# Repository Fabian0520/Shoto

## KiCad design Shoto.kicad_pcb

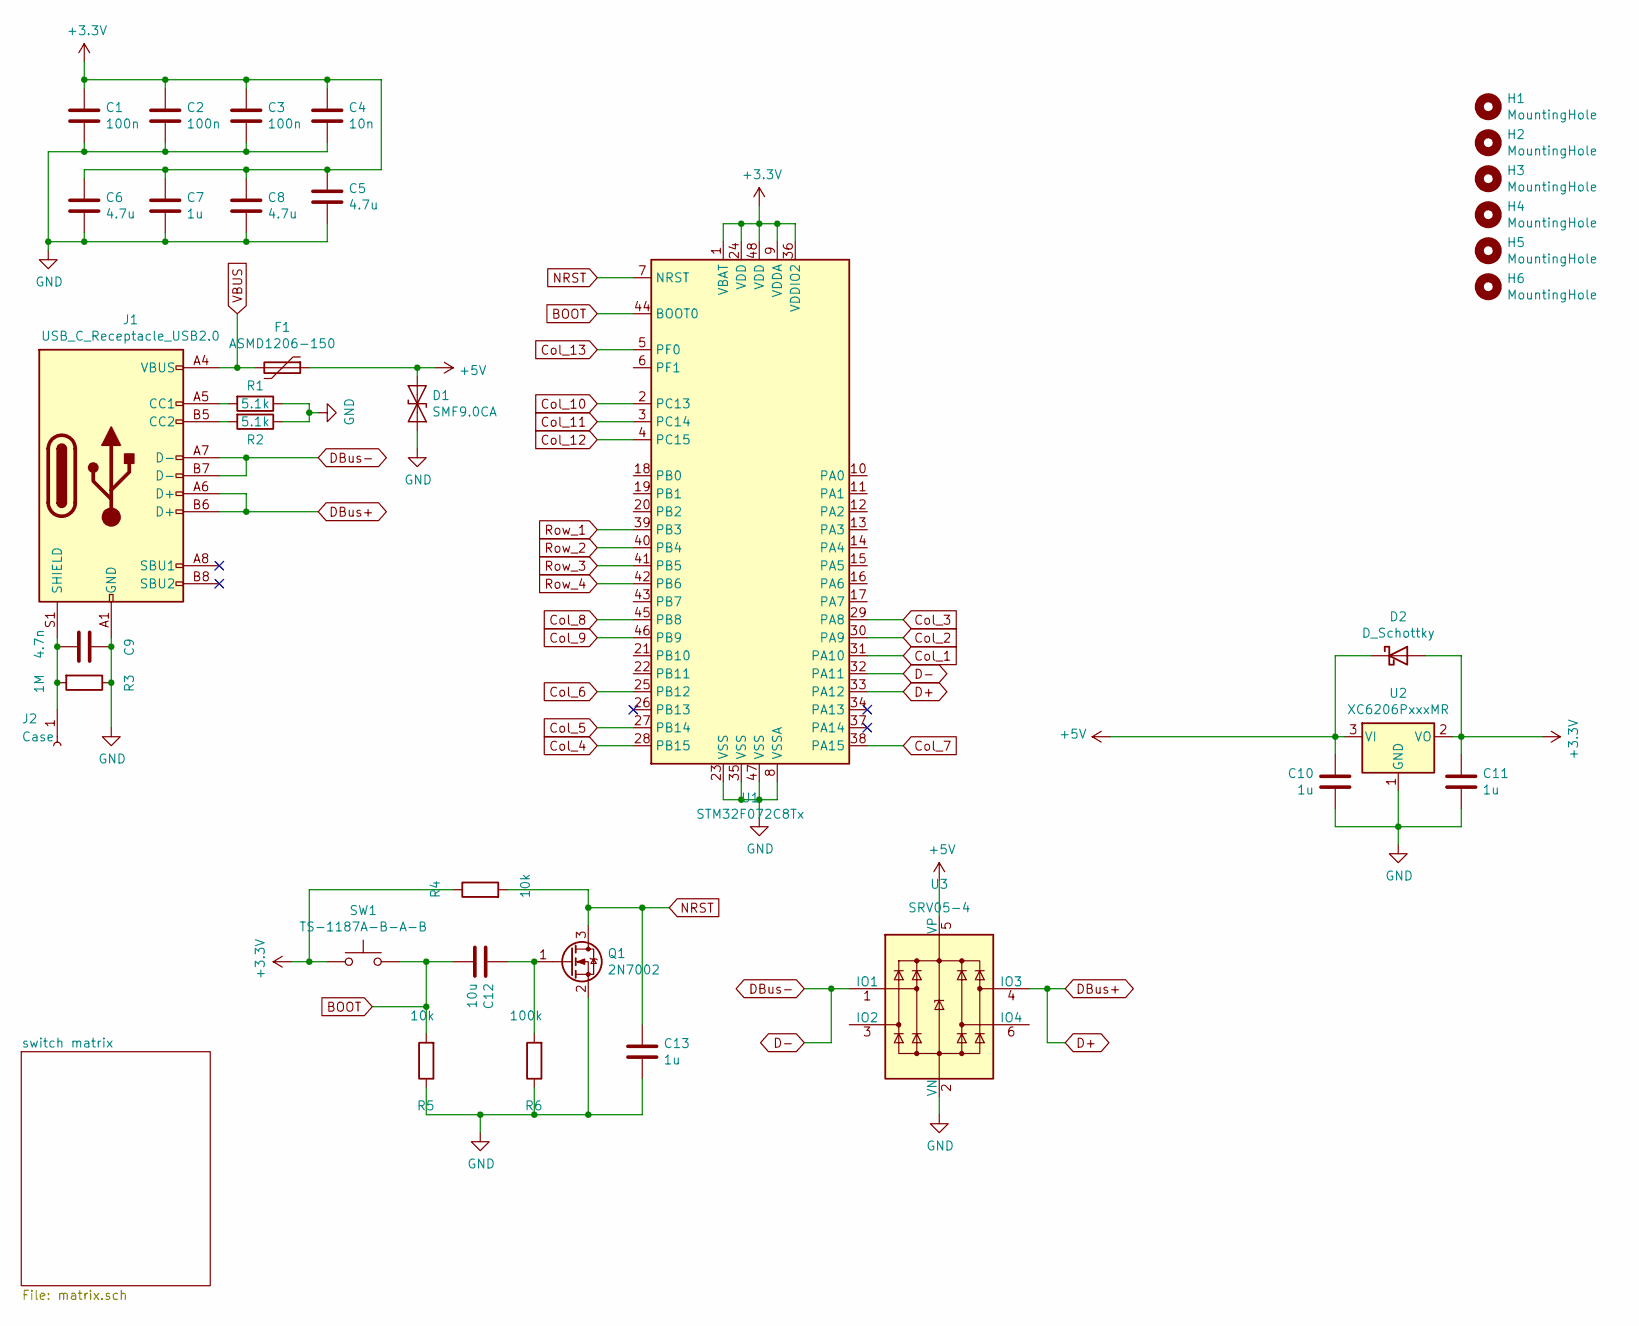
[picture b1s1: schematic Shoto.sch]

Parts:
C1, C2, C3: 100n; C_0603_1608Metric; JLCPCB C14663
C4: 10n; C_0603_1608Metric; JLCPCB C57112
C5, C6, C8: 4.7u; C_0603_1608Metric; JLCPCB C19666
C7, C10, C11, C13: 1u; C_0603_1608Metric; JLCPCB C15849
C9: 4.7n; C_0603_1608Metric; JLCPCB C53987
C12: 10u; C_0603_1608Metric; JLCPCB C19702
D1: SMF9.0CA; D_SOD-123; JLCPCB C123799
D2: D_Schottky; D_SOD-123; JLCPCB C8598
F1: ASMD1206-150; Fuse_1206_3216Metric; JLCPCB C135341
H1, H2, H3, H4, H5, H6: MountingHole; MountingHole_2.2mm_M2
J1: USB_C_Receptacle_USB2.0; USB_C_Receptacle_HRO_TYPE-C-31-M-12
J2: Case; MountingHole_2.2mm_M2_Pad
Q1: 2N7002; SOT-23; JLCPCB C8545
R1, R2: 5.1k; R_0603_1608Metric; JLCPCB C23186
R3: 1M; R_1206_3216Metric; JLCPCB C17927
R4, R5: 10k; R_0603_1608Metric; JLCPCB C25804
R6: 100k; R_0603_1608Metric; JLCPCB C25803
SW1: TS-1187A-B-A-B; SW_SPST_TL3342; JLCPCB C318884
U1: STM32F072C8Tx; LQFP-48_7x7mm_P0.5mm; JLCPCB C80488
U2: XC6206PxxxMR; SOT-23; JLCPCD C5446
U3: SRV05-4; SOT-23-6; JLCPCB C85364

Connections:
+3V3: C1.1, C2.1, C3.1, C4.1, C5.1, C6.1, C7.1, C8.1, C11.1, D2.2 (A), R4.1, SW1.1, U1.1 (VBAT), U1.9 (VDDA), U1.24 (VDD), U1.36 (VDDIO2), U1.48 (VDD), U2.2 (VO)
+5V: C10.1, D1.1 (A1), D2.1 (K), F1.1, U2.3 (VI), U3.5 (VP)
BOOT: C12.2, R5.2, SW1.2, U1.44 (BOOT0)
Col_1: U1.31 (PA10); also elsewhere on the board
Col_2: U1.30 (PA9); also elsewhere on the board
Col_3: U1.29 (PA8); also elsewhere on the board
Col_4: U1.28 (PB15); also elsewhere on the board
Col_5: U1.27 (PB14); also elsewhere on the board
Col_6: U1.25 (PB12); also elsewhere on the board
Col_7: U1.38 (PA15); also elsewhere on the board
Col_8: U1.45 (PB8); also elsewhere on the board
Col_9: U1.46 (PB9); also elsewhere on the board
Col_10: U1.2 (PC13); also elsewhere on the board
Col_11: U1.3 (PC14); also elsewhere on the board
Col_12: U1.4 (PC15); also elsewhere on the board
Col_13: U1.5 (PF0); also elsewhere on the board
D+: J1.A6 (D+), J1.B6 (D+), U1.33 (PA12), U3.4 (IO3)
D-: J1.A7 (D-), J1.B7 (D-), U1.32 (PA11), U3.1 (IO1)
GND: C1.2, C2.2, C3.2, C4.2, C5.2, C6.2, C7.2, C8.2, C9.1, C10.2, C11.2, C13.2, D1.2 (A2), J1.A1 (GND), J1.A12 (GND), J1.B1 (GND), J1.B12 (GND), Q1.2 (S), R1.1, R2.1, R3.1, R5.1, R6.1, U1.8 (VSSA), U1.23 (VSS), U1.35 (VSS), U1.47 (VSS), U2.1 (GND), U3.2 (VN)
NRST: C13.1, Q1.3 (D), R4.2, U1.7 (NRST)
unnamed: C9.2, J1.S1 (SHIELD), J2.1, R3.2
unnamed: C12.1, Q1.1 (G), R6.2
unnamed: J1.A5 (CC1), R1.2
unnamed: J1.B5 (CC2), R2.2
Row_1: U1.39 (PB3); also elsewhere on the board
Row_2: U1.40 (PB4); also elsewhere on the board
Row_3: U1.41 (PB5); also elsewhere on the board
Row_4: U1.42 (PB6); also elsewhere on the board
VBUS: F1.2, J1.A4 (VBUS), J1.A9 (VBUS), J1.B4 (VBUS), J1.B9 (VBUS)

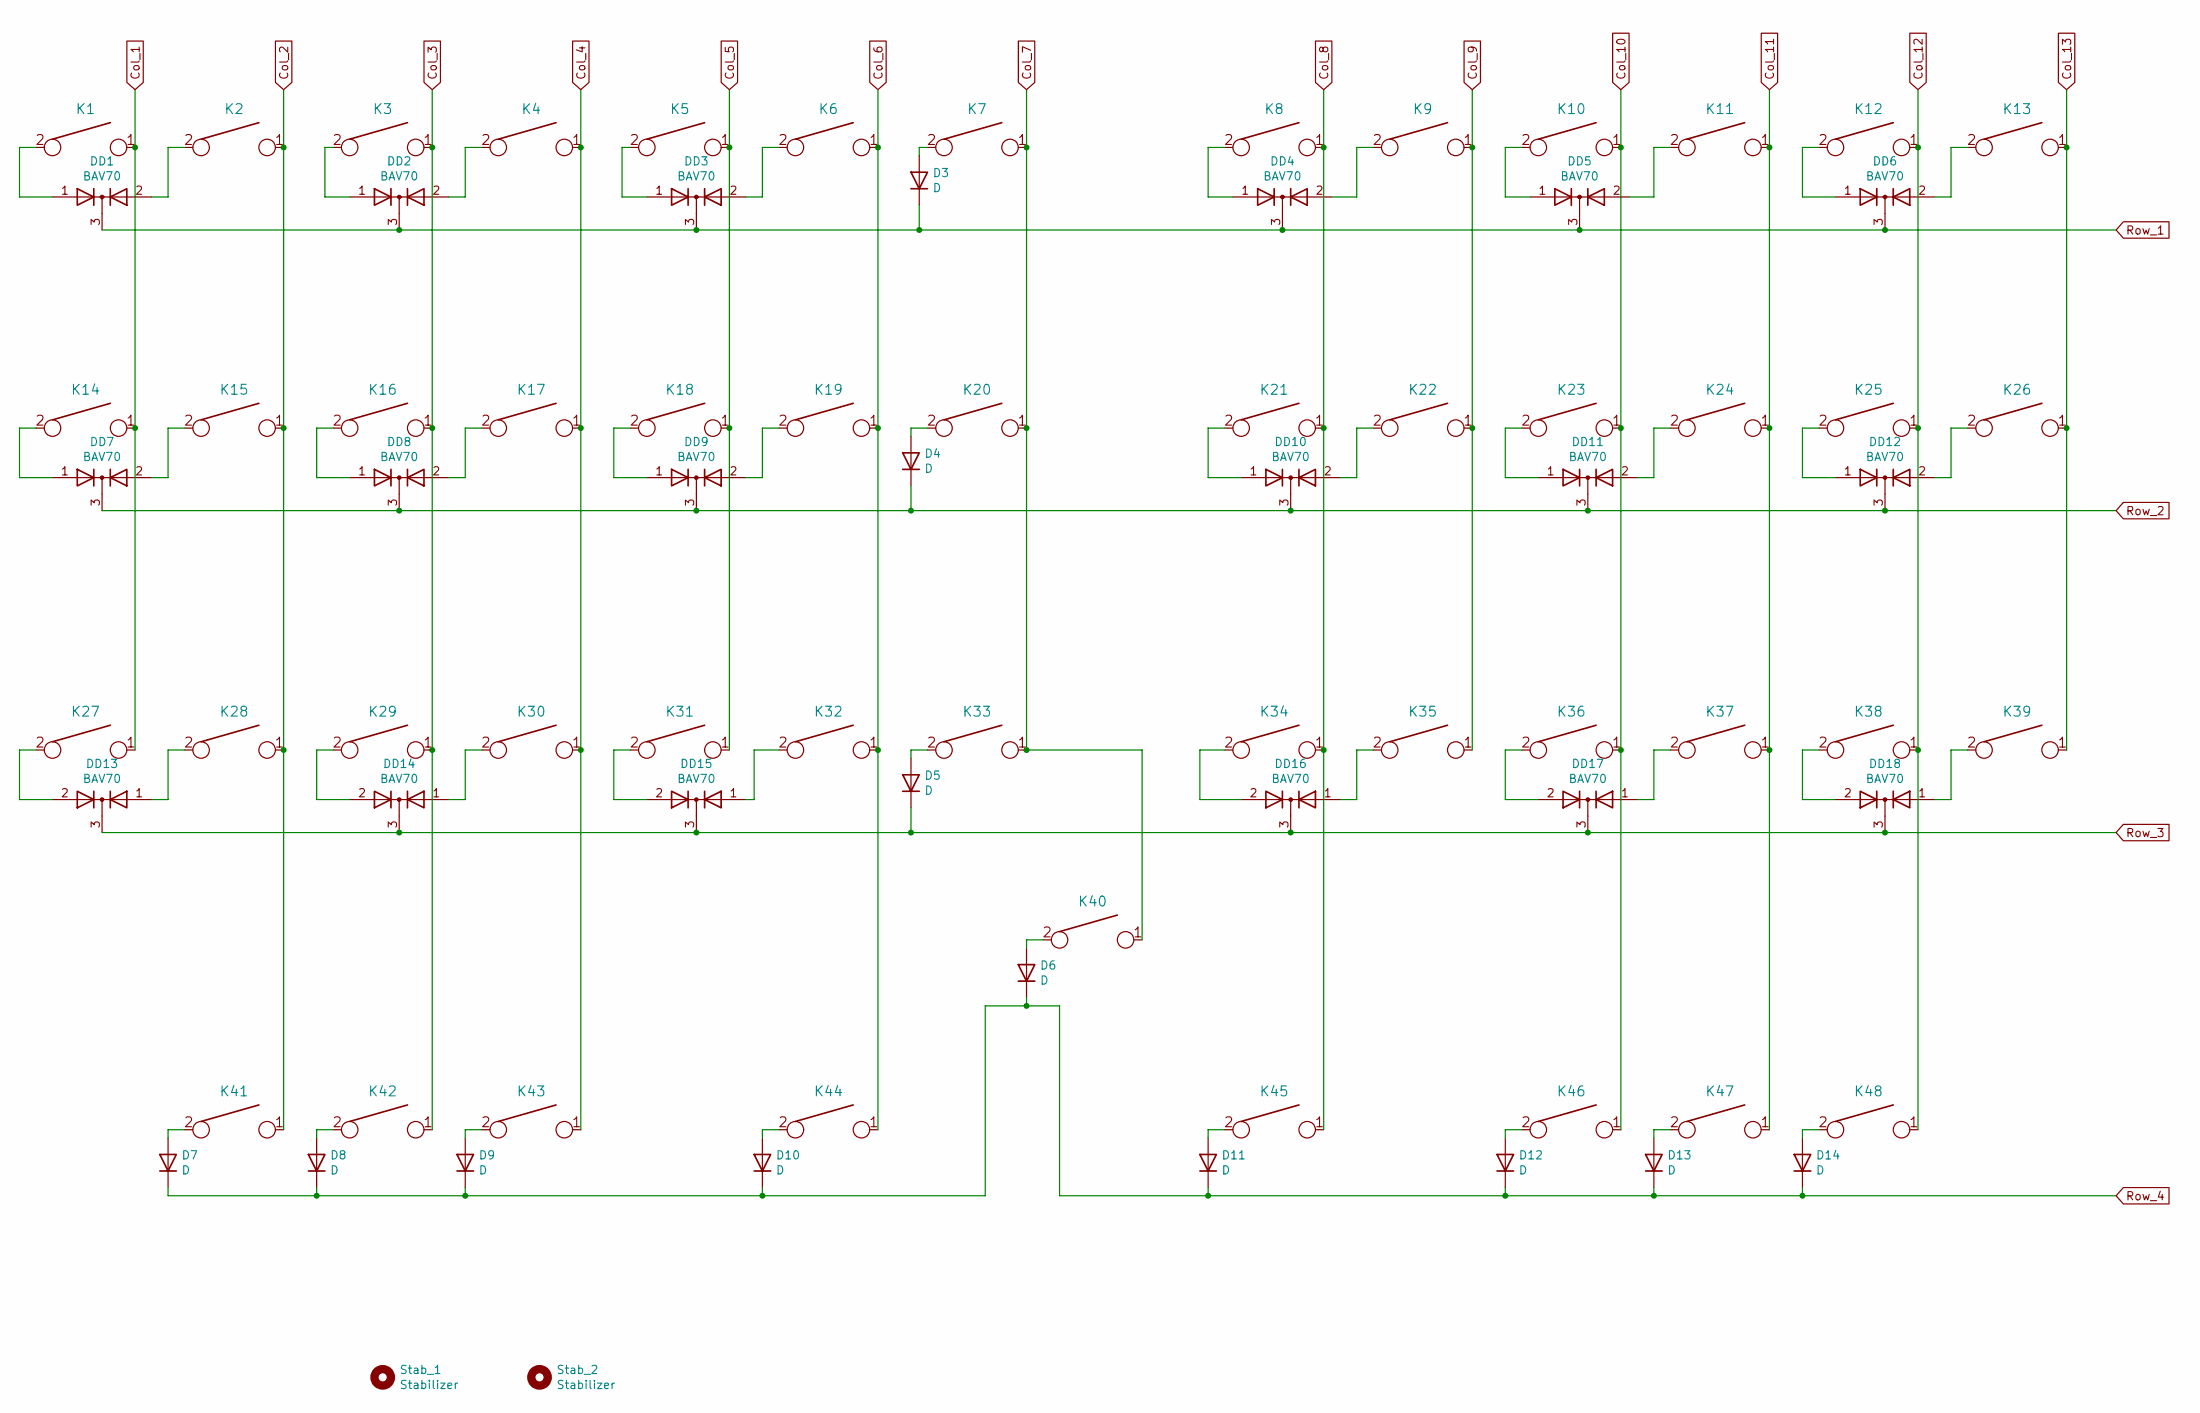
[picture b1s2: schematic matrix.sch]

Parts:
D3, D4, D5, D6, D7, D8, D9, D10, D11, D12, D13, D14: D; D_SOD-123; JLCPCB C8598
DD1, DD2, DD3, DD4, DD5, DD6, DD7, DD8, DD9, DD10, DD11, DD12, DD13, DD14, DD15, DD16, DD17, DD18: BAV70; SOT23-3_HSOL; JLCPCB C68978
K1, K2, K3, K4, K5, K6, K7, K8, K9, K10, K11, K12, K13, K14, K15, K16, K17, K18, K19, K20, K21, K22, K23, K24, K25, K26, K27, K28, K29, K30, K31, K32, K33, K34, K35, K36, K37, K38, K39, K40, K41, K42, K43, K44, K45, K46, K47, K48: KEYSW; Kailh_MX_Socket
Stab_1, Stab_2: Stabilizer; 2U-StabFlip

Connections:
Col_1: K1.1, K14.1, K27.1; also elsewhere on the board
Col_2: K2.1, K15.1, K28.1, K41.1; also elsewhere on the board
Col_3: K3.1, K16.1, K29.1, K42.1; also elsewhere on the board
Col_4: K4.1, K17.1, K30.1, K43.1; also elsewhere on the board
Col_5: K5.1, K18.1, K31.1; also elsewhere on the board
Col_6: K6.1, K19.1, K32.1, K44.1; also elsewhere on the board
Col_7: K7.1, K20.1, K33.1, K40.1; also elsewhere on the board
Col_8: K8.1, K21.1, K34.1, K45.1; also elsewhere on the board
Col_9: K9.1, K22.1, K35.1; also elsewhere on the board
Col_10: K10.1, K23.1, K36.1, K46.1; also elsewhere on the board
Col_11: K11.1, K24.1, K37.1, K47.1; also elsewhere on the board
Col_12: K12.1, K25.1, K38.1, K48.1; also elsewhere on the board
Col_13: K13.1, K26.1, K39.1; also elsewhere on the board
unnamed: D3.2 (A), K7.2
unnamed: D4.2 (A), K20.2
unnamed: D5.2 (A), K33.2
unnamed: D6.2 (A), K40.2
unnamed: D7.2 (A), K41.2
unnamed: D8.2 (A), K42.2
unnamed: D9.2 (A), K43.2
unnamed: D10.2 (A), K44.2
unnamed: D11.2 (A), K45.2
unnamed: D12.2 (A), K46.2
unnamed: D13.2 (A), K47.2
unnamed: D14.2 (A), K48.2
unnamed: DD1.1 (A), K1.2
unnamed: DD1.2 (A), K2.2
unnamed: DD2.1 (A), K3.2
unnamed: DD2.2 (A), K4.2
unnamed: DD3.1 (A), K5.2
unnamed: DD3.2 (A), K6.2
unnamed: DD4.1 (A), K8.2
unnamed: DD4.2 (A), K9.2
unnamed: DD5.1 (A), K10.2
unnamed: DD5.2 (A), K11.2
unnamed: DD6.1 (A), K12.2
unnamed: DD6.2 (A), K13.2
unnamed: DD7.1 (A), K14.2
unnamed: DD7.2 (A), K15.2
unnamed: DD8.1 (A), K16.2
unnamed: DD8.2 (A), K17.2
unnamed: DD9.1 (A), K18.2
unnamed: DD9.2 (A), K19.2
unnamed: DD10.1 (A), K21.2
unnamed: DD10.2 (A), K22.2
unnamed: DD11.1 (A), K23.2
unnamed: DD11.2 (A), K24.2
unnamed: DD12.1 (A), K25.2
unnamed: DD12.2 (A), K26.2
unnamed: DD13.1 (A), K28.2
unnamed: DD13.2 (A), K27.2
unnamed: DD14.1 (A), K30.2
unnamed: DD14.2 (A), K29.2
unnamed: DD15.1 (A), K32.2
unnamed: DD15.2 (A), K31.2
unnamed: DD16.1 (A), K35.2
unnamed: DD16.2 (A), K34.2
unnamed: DD17.1 (A), K37.2
unnamed: DD17.2 (A), K36.2
unnamed: DD18.1 (A), K39.2
unnamed: DD18.2 (A), K38.2
Row_1: D3.1 (K), DD1.3 (K), DD2.3 (K), DD3.3 (K), DD4.3 (K), DD5.3 (K), DD6.3 (K); also elsewhere on the board
Row_2: D4.1 (K), DD7.3 (K), DD8.3 (K), DD9.3 (K), DD10.3 (K), DD11.3 (K), DD12.3 (K); also elsewhere on the board
Row_3: D5.1 (K), DD13.3 (K), DD14.3 (K), DD15.3 (K), DD16.3 (K), DD17.3 (K), DD18.3 (K); also elsewhere on the board
Row_4: D6.1 (K), D7.1 (K), D8.1 (K), D9.1 (K), D10.1 (K), D11.1 (K), D12.1 (K), D13.1 (K), D14.1 (K); also elsewhere on the board

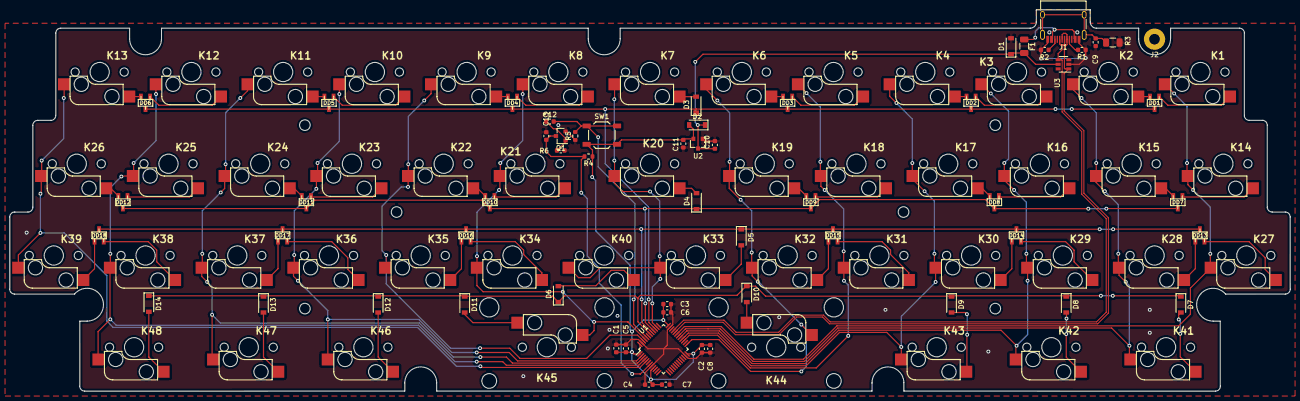
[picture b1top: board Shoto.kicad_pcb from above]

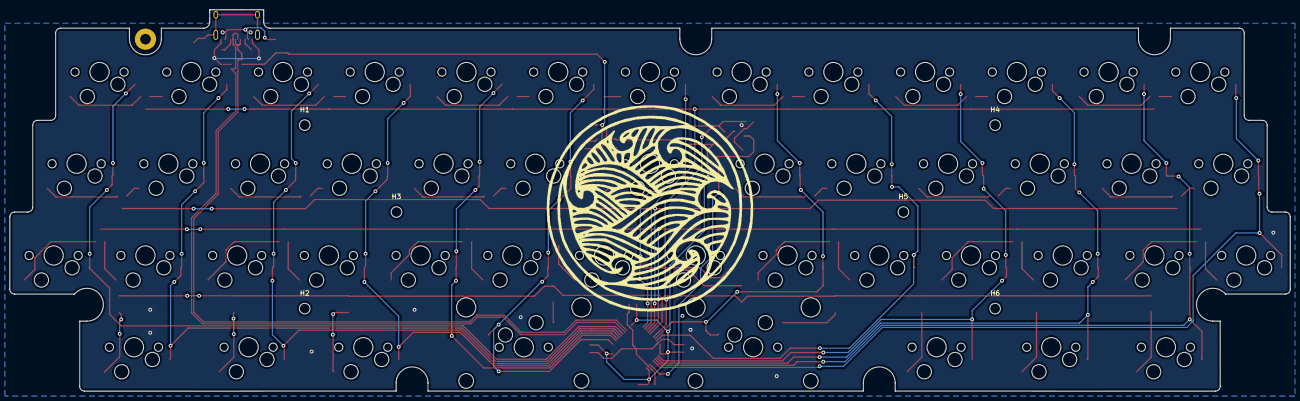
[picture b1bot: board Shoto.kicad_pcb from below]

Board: 2 copper layers, 265.2 x 79.0 mm, 115 parts (8 on the bottom side), 77 nets.

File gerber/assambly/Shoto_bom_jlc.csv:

"Comment","Designator","Footprint","LCSC Part #"
"100n","C1,C2,C3","C_0603_1608Metric","C14663"
"10n","C4","C_0603_1608Metric","C57112"
"4.7u","C6,C8,C5","C_0603_1608Metric","C19666"
"1u","C7,C11,C10,C13","C_0603_1608Metric","C15849"
"4.7n","C9","C_0603_1608Metric","C53987"
"10u","C12","C_0603_1608Metric","C19702"
"SMF9.0CA","D1","D_SOD-123","C123799"
"D_Schottky","D2","D_SOD-123","C8598"
"D","D3,D4,D5,D6,D7,D8,D9,D10,D11,D12,D13,D14","D_SOD-123","C8598"
"BAV70","DD1,DD7,DD8,DD9,DD13,DD15,DD16,DD17,DD18,DD14,DD10,DD11,DD12,DD6,DD5,DD4,DD3,DD2","SOT23-3_HSOL","C68978"
"ASMD1206-150","F1","Fuse_1206_3216Metric","C135341"
"2N7002","Q1","SOT-23","C8545"
"5.1k","R1,R2","R_0603_1608Metric","C23186"
"1M","R3","R_1206_3216Metric","C17927"
"10k","R5,R4","R_0603_1608Metric","C25804"
"100k","R6","R_0603_1608Metric","C25803"
"TS-1187A-B-A-B","SW1","SW_SPST_TL3342","C318884"
"STM32F072C8Tx","U1","LQFP-48_7x7mm_P0.5mm","C80488"
"XC6206PxxxMR","U2","SOT-23","C5446"
"SRV05-4","U3","SOT-23-6","C85364"

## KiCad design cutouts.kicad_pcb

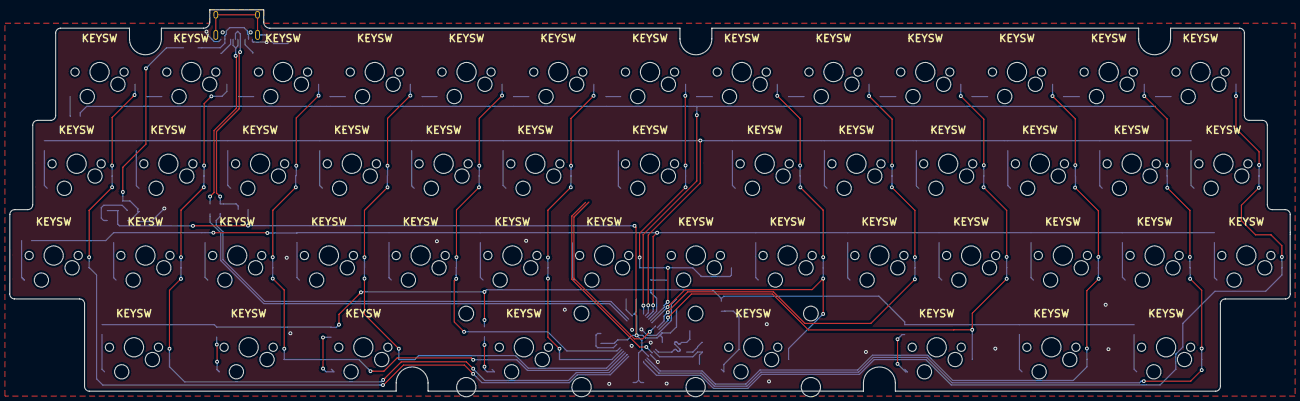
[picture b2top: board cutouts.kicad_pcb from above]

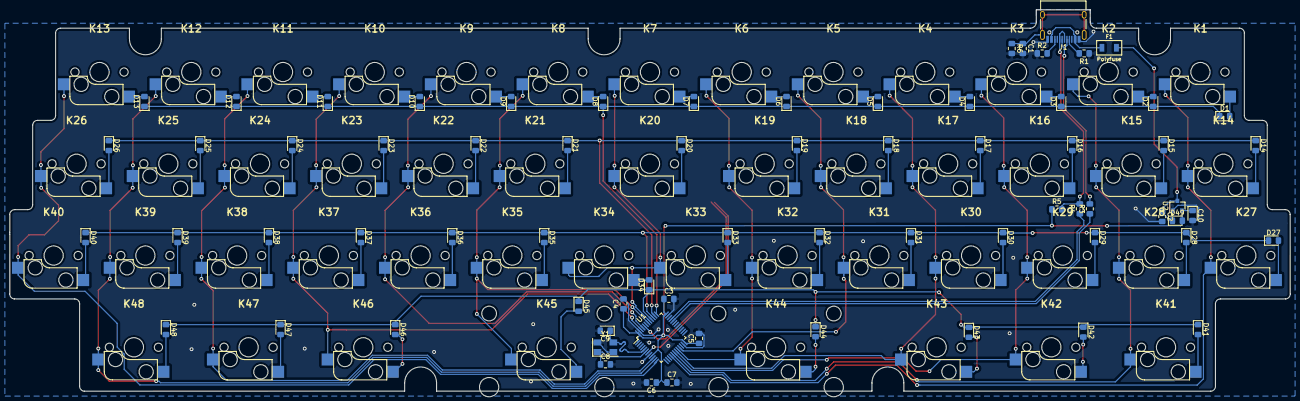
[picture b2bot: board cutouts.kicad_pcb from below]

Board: 2 copper layers, 265.2 x 79.0 mm, 118 parts (118 on the bottom side), 78 nets.

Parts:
C1: 4.7n; C_0805_2012Metric_Pad1.15x1.40mm_HandSolder
C2, C3, C4, C5, C6: 100n; C_0805_2012Metric_Pad1.15x1.40mm_HandSolder
C7: 4.7u; C_0805_2012Metric_Pad1.15x1.40mm_HandSolder
C8: 22p; C_0805_2012Metric_Pad1.15x1.40mm_HandSolder
C9: 22p; D_0805_2012Metric_Pad1.15x1.40mm_HandSolder
C10: 100n; D_0805_2012Metric_Pad1.15x1.40mm_HandSolder
D1, D2, D3, D4, D5, D6, D7, D8, D9, D10, D11, D12, D13, D14, D15, D16, D17, D18, D19, D20, D21, D22, D23, D24, D25, D26, D27, D28, D29, D30, D31, D32, D33, D34, D35, D36, D37, D38, D39, D40, D41, D42, D43, D44, D45, D46, D47, D48: D; D_0805_2012Metric_Pad1.15x1.40mm_HandSolder
D49: 1N4148; D_0805_2012Metric_Pad1.15x1.40mm_HandSolder
F1: Polyfuse; PPTC_nano
J1: USB_C_Receptacle_USB2.0; USB_C_Receptacle_HRO_TYPE-C-31-M-12
K1, K2, K3, K4, K5, K6, K7, K8, K9, K10, K11, K12, K13, K14, K15, K16, K17, K18, K19, K20, K21, K22, K23, K24, K25, K26, K27, K28, K29, K30, K31, K32, K33, K34, K35, K36, K37, K38, K39, K40, K41, K42, K43, K44, K45, K46, K47, K48: KEYSW; Kailh_MX_Socket
R1, R2: 5.1k; R_0805_2012Metric_Pad1.15x1.40mm_HandSolder
R3, R4: 22; R_0805_2012Metric_Pad1.15x1.40mm_HandSolder
R5: 1.5k; R_0805_2012Metric_Pad1.15x1.40mm_HandSolder
R6: 1M; R_0805_2012Metric_Pad1.15x1.40mm_HandSolder
U1: STM32F303CCTx; LQFP-48_7x7mm_P0.5mm
U2: MCP1700-3302E_SOT23; SOT-23
Y1: Crystal_GND24; Crystal_SMD_5032-4Pin_5.0x3.2mm

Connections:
+3V3: C3.1, C4.1, C5.1, C6.1, C7.1, C10.1, D49.2, R5.1, U1.1, U1.9, U1.24, U1.36, U1.48, U2.2
+5V: C2.1, D49.1, F1.1, U2.3
Col_1: K1.1, K14.1, K27.1, U1.16
Col_2: K2.1, K15.1, K28.1, K41.1, U1.17
Col_3: K3.1, K16.1, K29.1, K42.1, U1.18
Col_4: K4.1, K17.1, K30.1, K43.1, U1.19
Col_5: K5.1, K18.1, K31.1, U1.21
Col_6: K6.1, K19.1, K32.1, K44.1, U1.20
Col_7: K7.1, K20.1, K33.1, K34.1, U1.41
Col_8: K8.1, K21.1, K35.1, K45.1, U1.42
Col_9: K9.1, K22.1, K36.1, U1.45
Col_10: K10.1, K23.1, K37.1, K46.1, U1.46
Col_11: K11.1, K24.1, K38.1, K47.1, U1.10
Col_12: K12.1, K25.1, K39.1, K48.1, U1.11
Col_13: K13.1, K26.1, K40.1, U1.12
D+: R4.1, U1.33
D-: R3.1, U1.32
GND: C1.2, C2.2, C3.2, C4.2, C5.2, C6.2, C7.2, C8.2, C9.2, C10.2, J1.A1, J1.A12, J1.B1, J1.B12, R1.1, R2.1, R6.2, U1.8, U1.23, U1.35, U1.47, U2.1, Y1.2, Y1.4
unnamed: C1.1, J1.S1, R6.1
unnamed: D1.2, K1.2
unnamed: D2.2, K2.2
unnamed: D3.2, K3.2
unnamed: D4.2, K4.2
unnamed: D5.2, K5.2
unnamed: D6.2, K6.2
unnamed: D7.2, K7.2
unnamed: D8.2, K8.2
unnamed: D9.2, K9.2
unnamed: D10.2, K10.2
unnamed: D11.2, K11.2
unnamed: D12.2, K12.2
unnamed: D13.2, K13.2
unnamed: D14.2, K14.2
unnamed: D15.2, K15.2
unnamed: D16.2, K16.2
unnamed: D17.2, K17.2
unnamed: D18.2, K18.2
unnamed: D19.2, K19.2
unnamed: D20.2, K20.2
unnamed: D21.2, K21.2
unnamed: D22.2, K22.2
unnamed: D23.2, K23.2
unnamed: D24.2, K24.2
unnamed: D25.2, K25.2
unnamed: D26.2, K26.2
unnamed: D27.2, K27.2
unnamed: D28.2, K28.2
unnamed: D29.2, K29.2
unnamed: D30.2, K30.2
unnamed: D31.2, K31.2
unnamed: D32.2, K32.2
unnamed: D33.2, K33.2
unnamed: D34.2, K34.2
unnamed: D35.2, K35.2
unnamed: D36.2, K36.2
unnamed: D37.2, K37.2
unnamed: D38.2, K38.2
unnamed: D39.2, K39.2
unnamed: D40.2, K40.2
unnamed: D41.2, K41.2
unnamed: D42.2, K42.2
unnamed: D43.2, K43.2
unnamed: D44.2, K44.2
unnamed: D45.2, K45.2
unnamed: D46.2, K46.2
unnamed: D47.2, K47.2
unnamed: D48.2, K48.2
unnamed: J1.A5, R1.2
unnamed: J1.A6, J1.B6, R4.2, R5.2
unnamed: J1.A7, J1.B7, R3.2
unnamed: J1.B5, R2.2
Row_1: D1.1, D2.1, D3.1, D4.1, D5.1, D6.1, D7.1, D8.1, D9.1, D10.1, D11.1, D12.1, D13.1, U1.37
Row_2: D14.1, D15.1, D16.1, D17.1, D18.1, D19.1, D20.1, D21.1, D22.1, D23.1, D24.1, D25.1, D26.1, U1.38
Row_3: D27.1, D28.1, D29.1, D30.1, D31.1, D32.1, D33.1, D35.1, D36.1, D37.1, D38.1, D39.1, D40.1, U1.39
Row_4: D34.1, D41.1, D42.1, D43.1, D44.1, D45.1, D46.1, D47.1, D48.1, U1.40
VBUS: F1.2, J1.A4, J1.A9, J1.B4, J1.B9
XTAL1: C9.1, U1.5, Y1.3
XTAL2: C8.1, U1.6, Y1.1

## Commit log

2019-12-18 init
2021-01-25 ready for production
2021-02-20 working and produced unit
